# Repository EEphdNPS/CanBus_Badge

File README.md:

# CanBus_Badge
As we develop a badge for the upcoming event, I will post my eagle files, bill of materials, and source code here.

I developed the board and schematic in Eagle 7.6.0 light.

This board is based on Microchip's AN212 reference design (http://ww1.microchip.com/downloads/en/AppNotes/00212c.pdf)

Overview: The objective of this project is to build a controller area network (CAN) node that can be used during our upcoming hack-a-thon event. Each CAN node is powered by one 9 volt battery. The CAN node has one input and one output. The input is a photoresistor (R12) that is part of a voltage divider. The PIC microcontroller does an analog to digital conversion based on the output of the voltage divider. The CAN node output is a PWM-driven LED (add the part number from the BOM and schematic). The CAN ID of the node is based on the dip switches. The first two switches define the CAN ID when the node transmits the result of the A/D conversion. The last two switches determine which CAN ID the node will receive. The results of A/D conversion are transmitted onto the CAN bus and received by the proper CAN node. The CAN node uses this value to set the pulse width of the on pulse.

5V power regulation:
The current design of the badge uses a 7805 chip to take the 9V battery output and produce 5V for the badge to run. As a note, because the node is powered at 5V, the CAN bus high and low will have a neutral value of 2.5V and the CAN bus high will be 5V and the CAN bus low will be 0V. Added to the power regulation portion of the design is a momentary push button that will indicate whether the badge is on or off. I have not calculated the life of the battery in this application, but during the development of the badge, I've only used one battery and I used one batter to run both nodes that I built. 

PIC 16F876:
The PIC microprocessor is the main chip on the board. The code is (will be) uploaded. The PIC talks to the MCP2515 chip via a SPI interface (pins 3-chip select, 14-SCK, 15-SDI, 16-SDO). Each line of the SPI interface has a test point, which we can use to access the SPI messages during the hack-a-thon. The PIC has one pin (pin 2) for the A/D conversion of the voltage divider. It has one pin (pin 13) as the PWM output. The chip receives a 4 MHz clock signal on pins 9 and 10. Pin 21 on the PIC is connected to the interrupt pin (pin 12) on the MCP2515. Pins 25 and 26 are connected are connected to the receive buffers on the MCP2515. Pins 11, 12, 17, 18 are connected to the DIP switches and are read to determine the transmit CAN ID and which CAN ID will be received. 

MCP2515:
The MCP2515 is the CAN controller chip and handles all CAN messaging. Pins 1 and 2 are connected to the MCP2551. The LEDs off of these lines are used as a visual indication that there is communication between these two chips. There are also test points added to these lines to access the messages being transmitted and received between the two chips. This chip operates with a 16 MHz oscillator on pins 7 and 8. I believe this frequency determines the bit rate on the CAN bus. I added a momentary button to the reset pin because occasionally the chip won't go into normal mode from startup mode. After reading the documentation, the chip needs a bus to be connected before going into normal mode. The reset button let you turn on the node first and then connect it to the bus. Once the bus is connected, I've found that one press of the reset button allows the chip to transition.

MCP2551:
The MCP2551 is a simple chip that interfaces with the CAN bus. This chip is probably not actually needed in this design. I have not tested whether or not it is required. We could probably skip it and connect the MCP2515 directly to another MCP2515 on another node. Pin 6 in the CAN low pin. Pin 7 is the CAN high pin. Pin 8 must be connected to ground via 10K ohm resistor. This pin sets the various modes of the MCP2551 chip. Without this resistor the CAN nodes will not communicate properly. 

CAN Bus:
To build the CAN bus, two 120 ohm resistors are required. These two resistors connect the high and low CAN bus wires at the termination of each end of the bus. At this point, I do not know a limit on the number of nodes that can be added to the bus without significant collisions. I have tested two nodes. If we have more, we could determine the max number that can be added. After trying several different configurations, I've settled on directly connecting the badges. There is no need for the 120 ohm resistors.

I've used the CanaKit UK1300 to program the PICs that I used on my breadboard. The ICSP works on the breadboard I've been developing from. I was not able to test it with Rev 1.0. I used the PICKit 3.

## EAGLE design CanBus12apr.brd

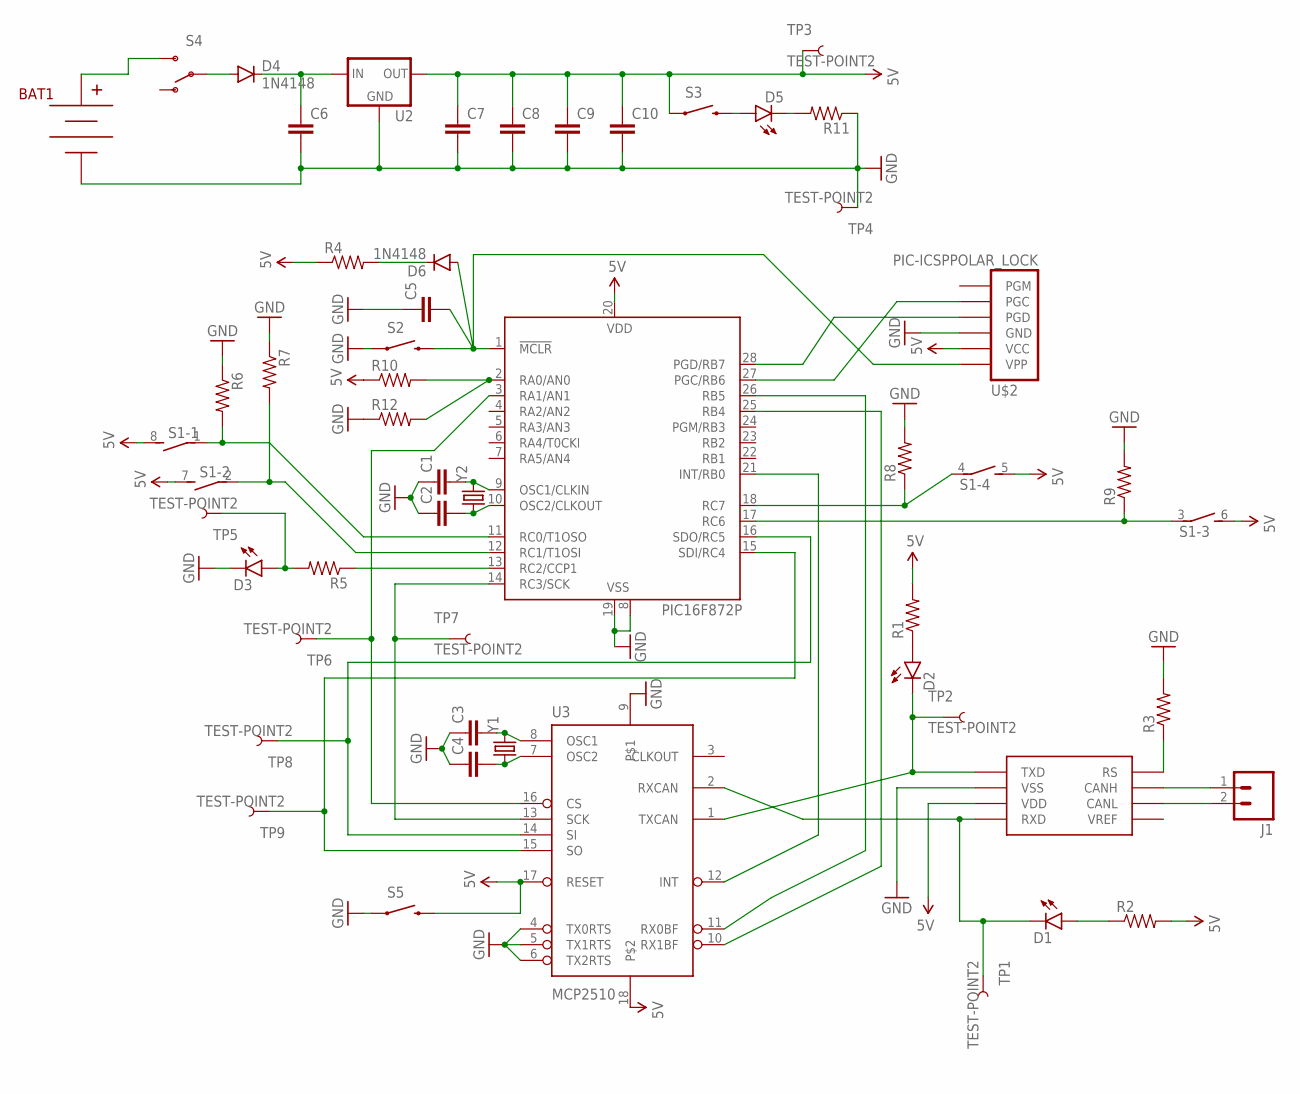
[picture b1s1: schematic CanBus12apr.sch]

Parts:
BAT1: BC9VPC
C1, C2, C3, C4, C5, C6, C7, C8, C9, C10: CAPPTH; CAP-PTH-SMALL
D1, D2, D3, D5: LED5MM
D4, D6: 1N4148; DIODE-1N4148-KIT
IC1: PIC16F872P; DIL28-3
J1: M02PTH; 1X02
R1, R2, R3, R4, R5, R6, R7, R8, R9, R10, R11: RESISTOREZ; AXIAL-0.3EZ
R12: RESISTORAXIAL-0.3; AXIAL-0.3
S1: DIP04S
S2, S3, S5: SWITCH-MOMENTARY-2PTH; TACTILE-PTH
S4: SWITCH-SPDTKIT; SWITCH-SPDT_KIT
TP1, TP2, TP3, TP4, TP5, TP6, TP7, TP8, TP9: TEST-POINT2; PAD.02X.02
U2: V_REG_78XXSIDE; 78XXL
U3: MCP2510; DIL18
U$1: MCP2551
U$2: PIC-ICSPPOLAR_LOCK; MOLEX-1X6_LOCK
Y1, Y2: CRYSTALHC49UV; HC49U-V

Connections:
5V: C7.1, C8.1, C9.1, C10.1, IC1.20 (VDD), R1.P$2 (2), R2.P$2 (2), R4.P$1 (1), R10.P$1 (1), S1.5 (2), S1.6 (2), S1.7 (2), S1.8 (2), S3.1, S5.3 (2), TP3.P$1, U2.OUT, U3.17 (RESET), U3.18, U$1.VDD, U$2.5 (VCC)
GND: BAT1.V-, C1.1, C2.1, C3.1, C4.1, C5.1, C6.2, C7.2, C8.2, C9.2, C10.2, D3.K (C), IC1.8 (VSS), IC1.19 (VSS), R3.P$2 (2), R6.P$1 (1), R7.P$1 (1), R8.P$2 (2), R9.P$2 (2), R11.P$1 (1), R12.P$1 (1), S2.1, S5.1, TP4.P$1, U2.GND, U3.4 (TX0RTS), U3.5 (TX1RTS), U3.6 (TX2RTS), U3.9, U$1.VSS, U$2.4 (GND)
unnamed: D1.K (C), TP1.P$1, U3.2 (RXCAN), U$1.RXD
unnamed: D2.K (C), TP2.P$1, U3.1 (TXCAN), U$1.TXD
unnamed: D2.A, R1.P$1 (1)
unnamed: D1.A, R2.P$1 (1)
unnamed: IC1.21 (INT/RB0), U3.12 (INT)
unnamed: IC1.26 (RB5), U3.11 (RX0BF)
unnamed: IC1.25 (RB4), U3.10 (RX1BF)
unnamed: IC1.11 (RC0/T1OSO), R6.P$2 (2), S1.1
unnamed: R3.P$1 (1), U$1.RS
unnamed: IC1.2 (RA0/AN0), R10.P$2 (2), R12.P$2 (2)
unnamed: C3.2, U3.8 (OSC1), Y1.2
unnamed: C4.2, U3.7 (OSC2), Y1.1
unnamed: C1.2, IC1.9 (OSC1/CLKIN), Y2.2
unnamed: C2.2, IC1.10 (OSC2/CLKOUT), Y2.1
unnamed: IC1.14 (RC3/SCK), TP7.P$1, U3.13 (SCK)
unnamed: IC1.16 (SDO/RC5), TP8.P$1, U3.14 (SI)
unnamed: IC1.15 (SDI/RC4), TP9.P$1, U3.15 (SO)
unnamed: IC1.3 (RA1/AN1), TP6.P$1, U3.16 (CS)
unnamed: C5.2, D6.A, IC1.1 (!MCLR!), S2.3 (2), U$2.6 (VPP)
unnamed: IC1.13 (RC2/CCP1), R5.P$1 (1)
unnamed: D3.A, R5.P$2 (2), TP5.P$1
unnamed: IC1.27 (PGC/RB6), U$2.2 (PGC)
unnamed: IC1.12 (RC1/T1OSI), R7.P$2 (2), S1.2 (1)
unnamed: IC1.17 (RC6), R9.P$1 (1), S1.3 (1)
unnamed: IC1.18 (RC7), R8.P$1 (1), S1.4 (1)
unnamed: BAT1.V+, S4.3 (S)
unnamed: C6.1, D4.C, U2.IN
unnamed: D5.K (C), R11.P$2 (2)
unnamed: D4.A, S4.2
unnamed: D5.A, S3.3 (2)
unnamed: J1.1, U$1.CANH
unnamed: J1.2, U$1.CANL
unnamed: IC1.28 (PGD/RB7), U$2.3 (PGD)
unnamed: D6.C, R4.P$2 (2)

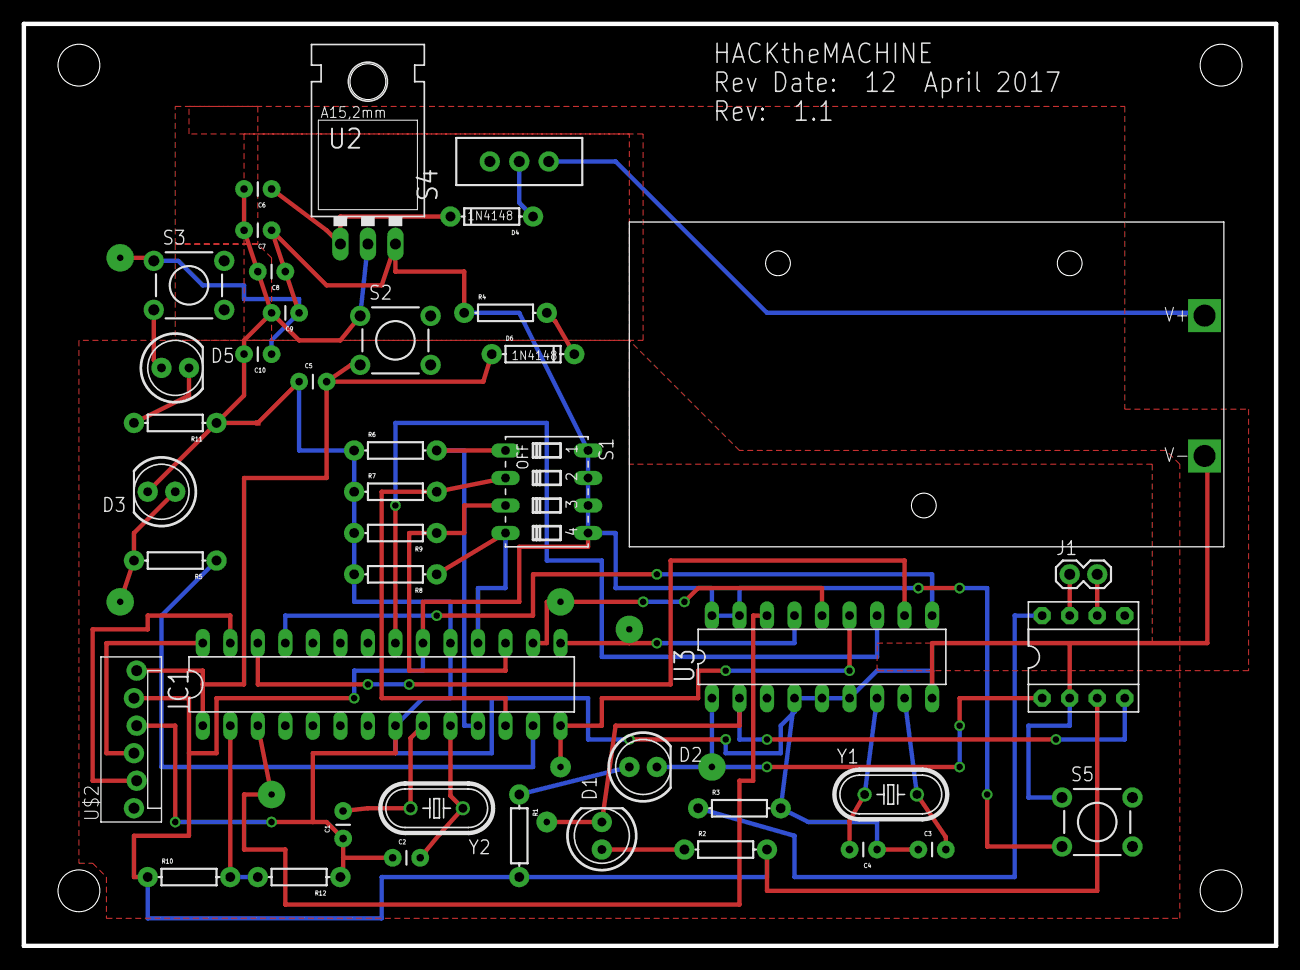
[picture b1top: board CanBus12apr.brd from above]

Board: 2 copper layers, 115.6 x 85.1 mm, 51 parts (0 on the bottom side), 36 nets.

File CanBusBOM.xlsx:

Part | Value | Device | Package | Description | MF | MPN
BAT1 |  | BC9VPC |  | 9V board-mount battery cradle | MPD | BC9VPC
C1 | 18 pF | CAPPTH | CAP-PTH-SMALL | Capacitor
C2 | 18 pF | CAPPTH | CAP-PTH-SMALL | Capacitor
C3 | 18 pF | CAPPTH | CAP-PTH-SMALL | Capacitor
C4 | 18 pF | CAPPTH | CAP-PTH-SMALL | Capacitor
C5 | 0.001 μF | CAPPTH | CAP-PTH-SMALL | Capacitor
C6 | 0.1 μF | CAPPTH | CAP-PTH-SMALL | Capacitor
C7 | 10 μF | CAPPTH | CAP-PTH-SMALL | Electrolytic Capacitor
C8 | 0.1 μF | CAPPTH | CAP-PTH-SMALL | Capacitor
C9 | 0.1 μF | CAPPTH | CAP-PTH-SMALL | Capacitor
C10 | 0.1 μF | CAPPTH | CAP-PTH-SMALL | Capacitor
D1 |  | Green LED5MM | LED5MM | LED used to visually display CAN receive
D2 |  | Blue LED5MM | LED5MM | LED used to visually display CAN transmit
D3 |  | Yellow LED5MM | LED5MM | LED driven by PWM output of PIC
D4 |  | GF1 | surface mount | DIODE | Vishay | GF1D-E3/67A
D5 |  | Blue LED5MM | LED5MM | LED used to test 5V power output
IC1 |  | PIC16F872P | DIL28-3 | MICROCONTROLLER | Microchip | PIC16F872-I/SP
Q2 |  | TRANSISTOR_PNPTO92 | TO-92 | Reg, 5V, .1A | Fairchild | LM78L05ACZ
R1 | 1k Ω | RESISTOREZ | AXIAL-0.3EZ | Resistor
R2 | 1k Ω | RESISTOREZ | AXIAL-0.3EZ | Resistor
R3 | 1k Ω | RESISTOREZ | AXIAL-0.3EZ | Resistor
R4 | 47k Ω | RESISTOREZ | AXIAL-0.3EZ | Resistor
R5 | 1k Ω | RESISTOREZ | AXIAL-0.3EZ | Resistor
R6 | 10k Ω | RESISTOREZ | AXIAL-0.3EZ | Resistor
R7 | 10k Ω | RESISTOREZ | AXIAL-0.3EZ | Resistor
R8 | 10k Ω | RESISTOREZ | AXIAL-0.3EZ | Resistor
R9 | 10k Ω | RESISTOREZ | AXIAL-0.3EZ | Resistor
R10 | 47k Ω | RESISTOREZ | AXIAL-0.3EZ | Used in voltage divider; need to match photoresitor
R11 | 1k Ω | RESISTOREZ | AXIAL-0.3EZ | Resistor
R12 | ~300 to 50k Ω | RESISTORAXIAL-0.3 | AXIAL-0.3 | photoresitor - used in voltage divider; need to test this resisitor to match wi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
S1 |  | SPST switch | surface mount | on/off switch | SMD | COM-12992
S2 |  | SWITCH-MOMENTARY-2PTH | TACTILE-PTH | momentary switch to reset pic (Master Clear - MCLR) | E-switch | TL1105EF250Q
S3 |  | SWITCH-MOMENTARY-2PTH | TACTILE-PTH | momentary switch to test 5V power supply | E-switch | TL1105EF250Q
SW1 |  | SWITCH_SPST_4_PINSQUARE | TACTILE-SWITCH-SMD | 4 position dip switch used to indicate CAN ID - switch 1 and 2 are used to set 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 | CTS | 206-4ST
TP1 |  | TEST-POINT2 | PAD.02X.02 | RXCAN on MCP2515
TP2 |  | TEST-POINT2 | PAD.02X.02 | TXCAN on MCP2515
TP3 |  | TEST-POINT2 | PAD.02X.02 | Bare copper test points for troubleshooting or ICT
TP4 |  | TEST-POINT2 | PAD.02X.02 | Bare copper test points for troubleshooting or ICT
TP5 |  | TEST-POINT2 | PAD.02X.02 | PWM output
TP6 |  | TEST-POINT2 | PAD.02X.02 | PIC to MCP2515 chip select (CS)
TP7 |  | TEST-POINT2 | PAD.02X.02 | PIC to MCP2515 clock (SCK)
TP8 |  | TEST-POINT2 | PAD.02X.02 | PIC to MCP2515 input (SI)
TP9 |  | TEST-POINT2 | PAD.02X.02 | PIC to MCP2515 output (SO)
TP10 |  | TEST-POINT2 | PAD.02X.02 | CAN high - connect to CAN bus
TP11 |  | TEST-POINT2 | PAD.02X.02 | CAN low - connect to CAN bus
U$1 |  | MCP2551 | DIL8 | CAN Interface | Microchip | MCP2551-I/P
U1 |  | MCP2515 | DIL18 | CAN controller with SPI interface to any MCU. | Microchip | MCP2515-I/P
Y1 | 16 MHz | crystal oscillator | HC-49/US | 16 MHz oscillator for CAN controller
Y2 | 4 MHz | crystal oscillator | HC-49/US | 4 MHz oscillator for PIC

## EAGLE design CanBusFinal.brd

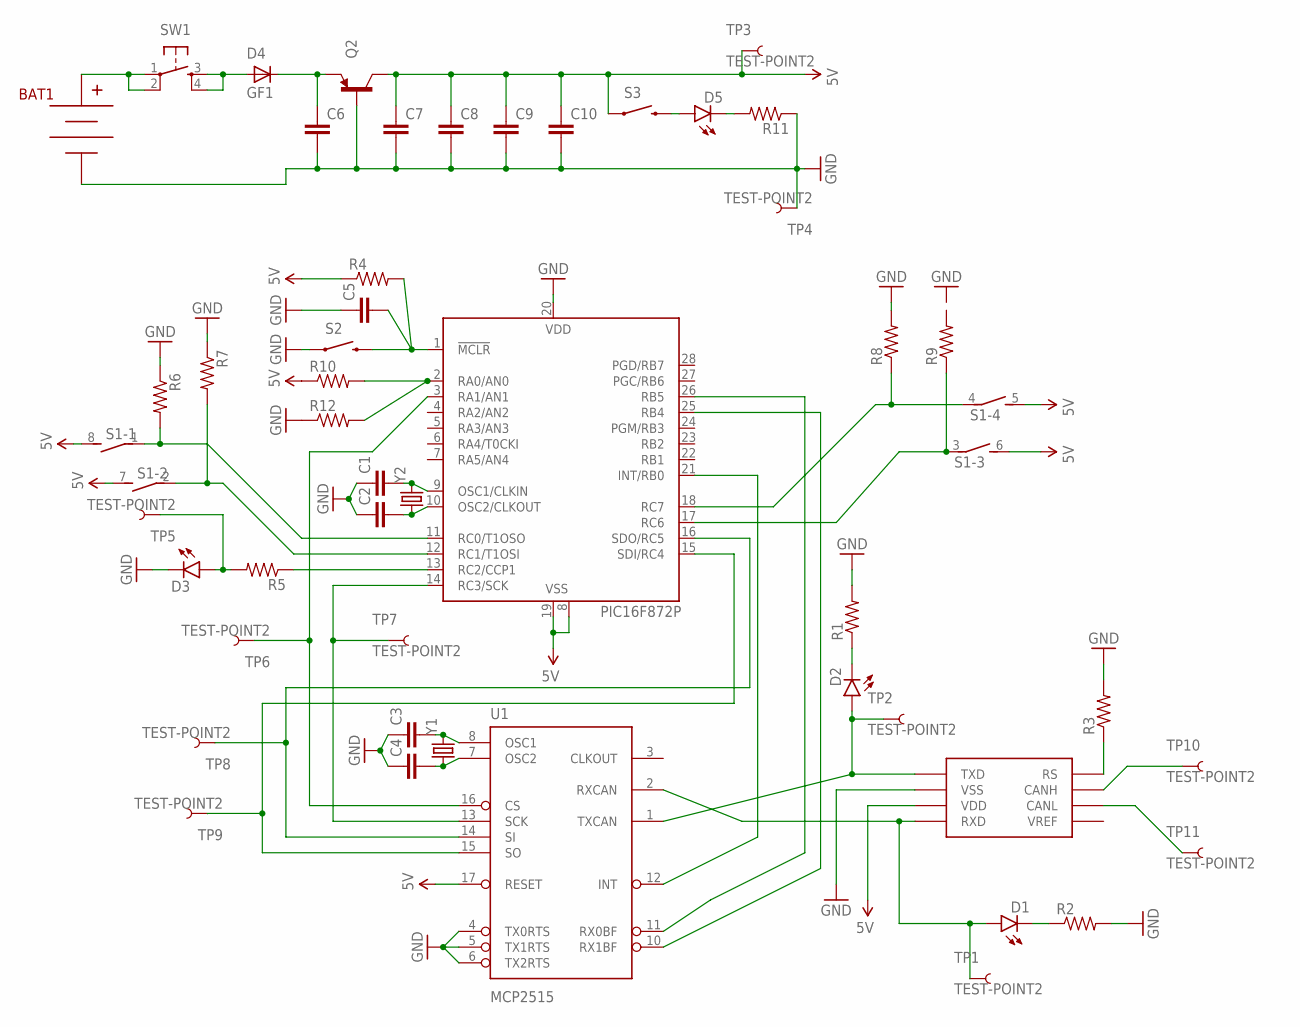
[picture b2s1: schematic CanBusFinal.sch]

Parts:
BAT1: BC9VPC
C1, C2, C3, C4, C5, C6, C7, C8, C9, C10: CAPPTH; CAP-PTH-SMALL
D1, D2, D3, D5: LED5MM
D4: GF1; SMA-DO214AC
IC1: PIC16F872P; DIL28-3
Q2: TRANSISTOR_PNPTO92; TO-92
R1, R2, R3, R4, R5, R6, R7, R8, R9, R10, R11: RESISTOREZ; AXIAL-0.3EZ
R12: RESISTORAXIAL-0.3; AXIAL-0.3
S1: DIP04S
S2, S3: SWITCH-MOMENTARY-2PTH; TACTILE-PTH
SW1: SWITCH_SPST_4_PINSQUARE; TACTILE-SWITCH-SMD
TP1, TP2, TP3, TP4, TP5, TP6, TP7, TP8, TP9, TP10, TP11: TEST-POINT2; PAD.02X.02
U1: MCP2515; DIL18
U$1: MCP2551
Y1, Y2: CRYSTALHC49UV; HC49U-V

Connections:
5V: C7.1, C8.1, C9.1, C10.1, IC1.8 (VSS), IC1.19 (VSS), Q2.3 (C), R4.P$1 (1), R10.P$1 (1), S1.5 (2), S1.6 (2), S1.7 (2), S1.8 (2), S3.1, TP3.P$1, U1.17 (RESET), U$1.VDD
GND: BAT1.V-, C1.1, C2.1, C3.1, C4.1, C5.1, C6.2, C7.2, C8.2, C9.2, C10.2, D3.K (C), IC1.20 (VDD), Q2.2 (B), R1.P$2 (2), R2.P$2 (2), R3.P$2 (2), R6.P$1 (1), R7.P$1 (1), R8.P$2 (2), R11.P$1 (1), R12.P$1 (1), S2.1, TP4.P$1, U1.4 (TX0RTS), U1.5 (TX1RTS), U1.6 (TX2RTS), U$1.VSS
unnamed: D1.A, TP1.P$1, U1.2 (RXCAN), U$1.RXD
unnamed: D2.A, TP2.P$1, U1.1 (TXCAN), U$1.TXD
unnamed: D2.K (C), R1.P$1 (1)
unnamed: D1.K (C), R2.P$1 (1)
unnamed: IC1.21 (INT/RB0), U1.12 (INT)
unnamed: IC1.26 (RB5), U1.11 (RX0BF)
unnamed: IC1.25 (RB4), U1.10 (RX1BF)
unnamed: IC1.11 (RC0/T1OSO), R6.P$2 (2), S1.1
unnamed: R3.P$1 (1), U$1.RS
unnamed: IC1.2 (RA0/AN0), R10.P$2 (2), R12.P$2 (2)
unnamed: C3.2, U1.8 (OSC1), Y1.2
unnamed: C4.2, U1.7 (OSC2), Y1.1
unnamed: C1.2, IC1.9 (OSC1/CLKIN), Y2.2
unnamed: C2.2, IC1.10 (OSC2/CLKOUT), Y2.1
unnamed: IC1.14 (RC3/SCK), TP7.P$1, U1.13 (SCK)
unnamed: IC1.16 (SDO/RC5), TP8.P$1, U1.14 (SI)
unnamed: IC1.15 (SDI/RC4), TP9.P$1, U1.15 (SO)
unnamed: IC1.3 (RA1/AN1), TP6.P$1, U1.16 (CS)
unnamed: C5.2, IC1.1 (!MCLR!), R4.P$2 (2), S2.3 (2)
unnamed: IC1.13 (RC2/CCP1), R5.P$1 (1)
unnamed: D3.A, R5.P$2 (2), TP5.P$1
unnamed: IC1.12 (RC1/T1OSI), R7.P$2 (2), S1.2 (1)
unnamed: IC1.17 (RC6), R9.P$1 (1), S1.3 (1)
unnamed: IC1.18 (RC7), R8.P$1 (1), S1.4 (1)
unnamed: D4.A, SW1.3, SW1.4
unnamed: C6.1, D4.K (C), Q2.1 (E)
unnamed: D5.K (C), R11.P$2 (2)
unnamed: BAT1.V+, SW1.1, SW1.2
unnamed: D5.A, S3.3 (2)
unnamed: TP11.P$1, U$1.CANL
unnamed: TP10.P$1, U$1.CANH
VDD: U1.18 (VDD)
VSS: U1.9 (VSS)

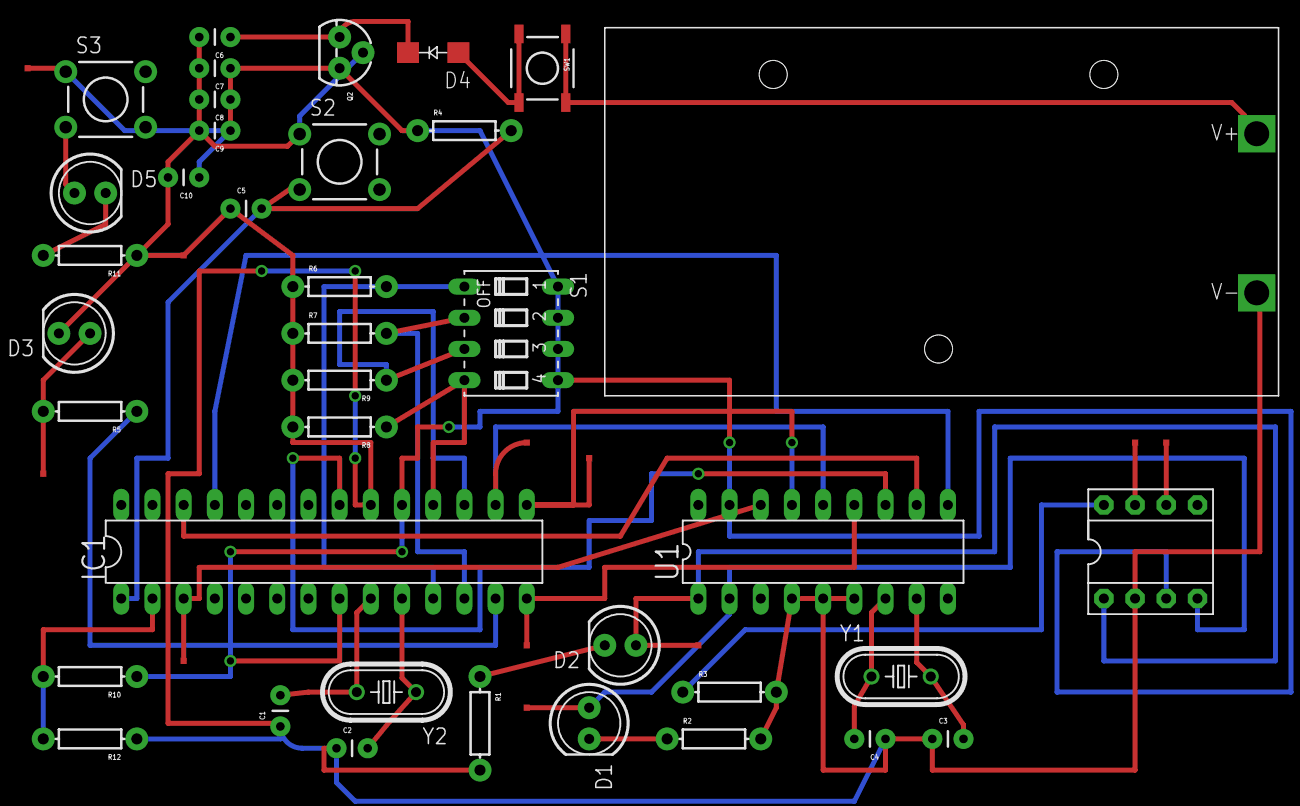
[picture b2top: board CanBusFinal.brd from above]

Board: 2 copper layers, 49 parts (0 on the bottom side), 33 nets.

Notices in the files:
parts and their libraries:
SparkFun-LED: Licensing: Creative Commons ShareAlike 4.0 International - https://creativecommons.org/licenses/by-sa/4.0
